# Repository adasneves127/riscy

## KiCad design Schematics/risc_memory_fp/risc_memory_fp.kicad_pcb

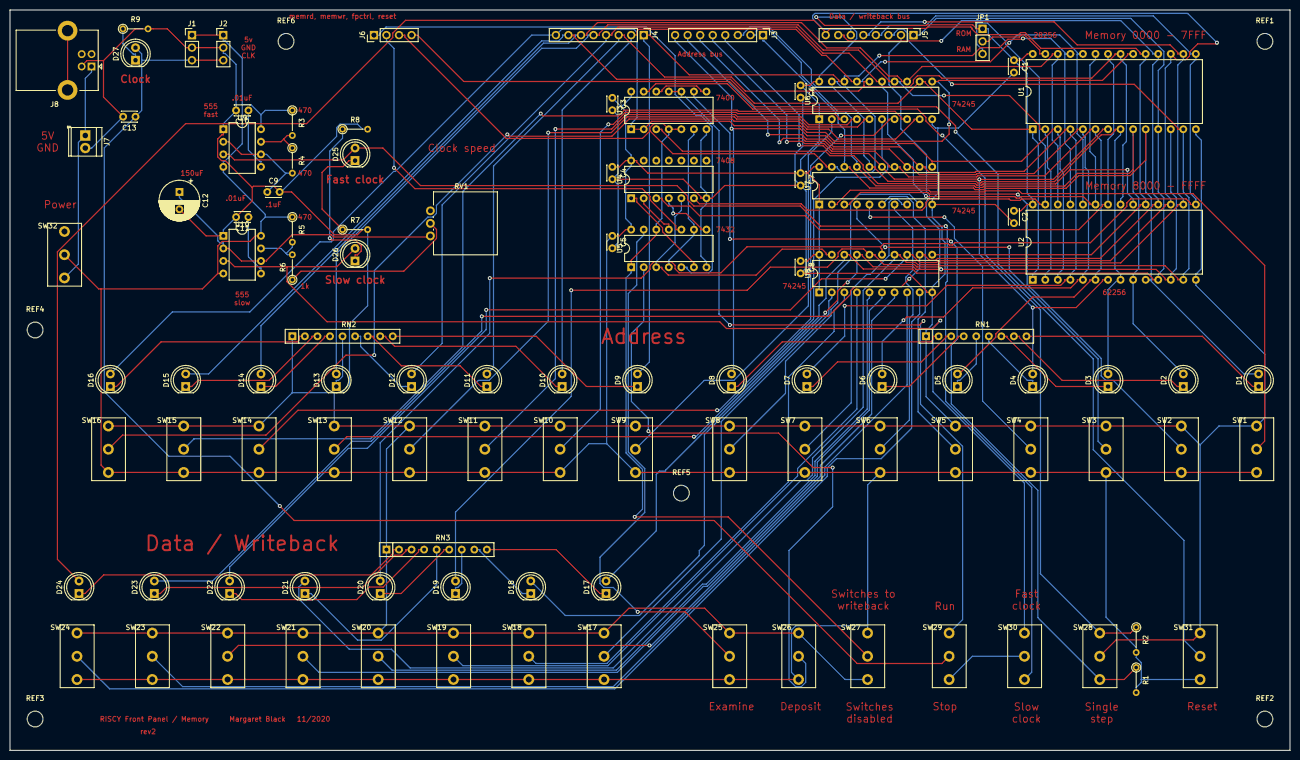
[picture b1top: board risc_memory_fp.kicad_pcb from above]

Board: 2 copper layers, 259.1 x 149.9 mm, 110 parts (0 on the bottom side), 108 nets.

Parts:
C1, C2, C3, C4, C5, C6, C7, C8: C; C_Disc_D3.0mm_W2.0mm_P2.50mm
C9: .1uF; C_Disc_D3.0mm_W2.0mm_P2.50mm
C10, C11: .01uF; C_Disc_D3.0mm_W2.0mm_P2.50mm
C12: 150uF; CP_Radial_D8.0mm_P3.50mm
C13: clocksmoothing; C_Disc_D3.0mm_W2.0mm_P2.50mm
D1, D2, D3, D4, D5, D6, D7, D8, D9, D10, D11, D12, D13, D14, D15, D16, D17, D18, D19, D20, D21, D22, D23, D24: LED; LED_D5.0mm
D25: Fastclock; LED_D5.0mm
D26: Slowclock; LED_D5.0mm
D27: Clock; LED_D5.0mm
J1, J2: Conn_01x03_Female; PinHeader_1x03_P2.54mm_Vertical
J3, J4, J5: Conn_01x08_Female; PinHeader_1x08_P2.54mm_Vertical
J6: Conn_01x04_Female; PinHeader_1x04_P2.54mm_Vertical
J7: Screw_Terminal_01x02; TerminalBlock_TE_282834-2_1x02_P2.54mm_Horizontal
J8: USB_B; USB_B_Lumberg_2411_02_Horizontal
JP1: Jumper_NC_Dual; PinHeader_1x03_P2.54mm_Vertical
R1, R2: 10k; R_Axial_DIN0204_L3.6mm_D1.6mm_P5.08mm_Vertical
R3, R4, R5: 470; R_Axial_DIN0204_L3.6mm_D1.6mm_P5.08mm_Vertical
R6, R7, R8, R9: 1k; R_Axial_DIN0204_L3.6mm_D1.6mm_P5.08mm_Vertical
REF1, REF2, REF3, REF4, REF5, REF6: MountingHole_3.2mm_M3
RN1, RN2, RN3: R_Network08; R_Array_SIP9
RV1: 4.7k; Potentiometer_Vishay_248GJ-249GJ_Single_Vertical
SW1, SW2, SW3, SW4, SW5, SW6, SW7, SW8, SW9, SW10, SW11, SW12, SW13, SW14, SW15, SW16, SW17, SW18, SW19, SW20, SW21, SW22, SW23, SW24, SW25, SW26, SW27, SW28, SW29, SW30, SW31, SW32: SW_SPDT; SPDT_toggle_switch_jameco_pcb_mounting
U1: 28C256; DIP-28_W15.24mm
U2: CY62256-70PC; DIP-28_W15.24mm
U3: 74LS00; DIP-14_W7.62mm
U4: 74LS08; DIP-14_W7.62mm
U5: 74LS32; DIP-14_W7.62mm
U6, U7, U8: 74LS245; DIP-20_W7.62mm
U9, U10: NE555P; DIP-8_W7.62mm

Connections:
+5V: C1.1, C2.1, C3.1, C4.1, C5.1, C6.1, C7.1, C8.1, J1.1, J2.1, JP1.1, R1.2, R2.2, R3.1, R5.1, SW1.3, SW2.3, SW3.3, SW4.3, SW5.3, SW6.3, SW7.3, SW8.3, SW9.3, SW10.3, SW11.3, SW12.3, SW13.3, SW14.3, SW15.3, SW16.3, SW17.3, SW18.3, SW19.3, SW20.3, SW21.3, SW22.3, SW23.3, SW24.3, SW25.3, SW26.3, SW27.1, SW31.3, SW32.2, U1.28, U2.28, U3.14, U4.14, U5.14, U6.1, U6.20, U7.1, U7.20, U8.1, U8.20, U9.4, U9.8, U10.4, U10.8
CLK: C13.1, D27.2, J1.3, J2.3, SW29.2
GND: C1.2, C2.2, C3.2, C4.2, C5.2, C6.2, C7.2, C8.2, C9.2, C10.2, C11.2, C12.2, C13.2, J1.2, J2.2, J7.2, J8.4, R7.2, R8.2, R9.2, RN1.1, RN2.1, RN3.1, SW1.1, SW2.1, SW3.1, SW4.1, SW5.1, SW6.1, SW7.1, SW8.1, SW9.1, SW10.1, SW11.1, SW12.1, SW13.1, SW14.1, SW15.1, SW16.1, SW17.1, SW18.1, SW19.1, SW20.1, SW21.1, SW22.1, SW23.1, SW24.1, SW25.1, SW26.1, SW27.3, SW28.2, SW31.1, U1.14, U2.14, U3.7, U4.7, U5.7, U6.10, U7.10, U8.10, U9.1, U10.1
unnamed: C9.1, R4.2, U9.2, U9.6
unnamed: C10.1, U9.5
unnamed: C11.1, U10.5
unnamed: C12.1, RV1.1, U10.2, U10.6
unnamed: D1.1, RN1.9
unnamed: D2.1, RN1.8
unnamed: D3.1, RN1.7
unnamed: D4.1, RN1.6
unnamed: D5.1, RN1.5
unnamed: D6.1, RN1.4
unnamed: D7.1, RN1.3
unnamed: D8.1, RN1.2
unnamed: D9.1, RN2.9
unnamed: D10.1, RN2.8
unnamed: D11.1, RN2.7
unnamed: D12.1, RN2.6
unnamed: D13.1, RN2.5
unnamed: D14.1, RN2.4
unnamed: D15.1, RN2.3
unnamed: D16.1, RN2.2
unnamed: D17.1, RN3.9
unnamed: D18.1, RN3.8
unnamed: D19.1, RN3.7
unnamed: D20.1, RN3.6
unnamed: D21.1, RN3.5
unnamed: D22.1, RN3.4
unnamed: D23.1, RN3.3
unnamed: D24.1, RN3.2
unnamed: D25.1, R7.1
unnamed: D25.2, SW30.3, U9.3
unnamed: D26.1, R8.1
unnamed: D26.2, SW30.1, U10.3
unnamed: D27.1, R9.1
unnamed: J7.1, J8.1, SW32.3
unnamed: JP1.2, U1.27
unnamed: R1.1, SW28.3, U3.9
unnamed: R2.1, SW28.1, U3.13
unnamed: R3.2, R4.1, U9.7
unnamed: R5.2, R6.2, U10.7
unnamed: R6.1, RV1.2
unnamed: SW1.2, U7.2
unnamed: SW2.2, U7.3
unnamed: SW3.2, U7.4
unnamed: SW4.2, U7.5
unnamed: SW5.2, U7.6
unnamed: SW6.2, U7.7
unnamed: SW7.2, U7.8
unnamed: SW8.2, U7.9
unnamed: SW9.2, U6.2
unnamed: SW10.2, U6.3
unnamed: SW11.2, U6.4
unnamed: SW12.2, U6.5
unnamed: SW13.2, U6.6
unnamed: SW14.2, U6.7
unnamed: SW15.2, U6.8
unnamed: SW16.2, U6.9
unnamed: SW17.2, U8.2
unnamed: SW18.2, U8.3
unnamed: SW19.2, U8.4
unnamed: SW20.2, U8.5
unnamed: SW21.2, U8.6
unnamed: SW22.2, U8.7
unnamed: SW23.2, U8.8
unnamed: SW24.2, U8.9
unnamed: SW29.1, U3.10, U3.11
unnamed: SW29.3, SW30.2
unnamed: U2.20, U3.3
unnamed: U3.6, U5.4, U5.9
unnamed: U3.8, U3.12
unnamed: U4.1, U5.6
unnamed: U4.2, U5.11
unnamed: U4.4, U5.8
addr0: D1.2, J3.1, U1.10, U2.10, U7.18
addr1: D2.2, J3.2, U1.9, U2.9, U7.17
addr2: D3.2, J3.3, U1.8, U2.8, U7.16
addr3: D4.2, J3.4, U1.7, U2.7, U7.15
addr4: D5.2, J3.5, U1.6, U2.6, U7.14
addr5: D6.2, J3.6, U1.5, U2.5, U7.13
addr6: D7.2, J3.7, U1.4, U2.4, U7.12
addr7: D8.2, J3.8, U1.3, U2.3, U7.11
addr8: D9.2, J4.1, U1.25, U2.25, U6.18
addr9: D10.2, J4.2, U1.24, U2.24, U6.17
addr10: D11.2, J4.3, U1.21, U2.21, U6.16
addr11: D12.2, J4.4, U1.23, U2.23, U6.15
addr12: D13.2, J4.5, U1.2, U2.2, U6.14
addr13: D14.2, J4.6, U1.26, U2.26, U6.13
addr14: D15.2, J4.7, U1.1, U2.1, U6.12
addr15: D16.2, J4.8, U1.20, U3.1, U3.2, U6.11
deposit: SW26.2, U5.2
examine: SW25.2, U5.13
fpcontrol: J6.3, SW27.2, U3.4, U3.5, U5.1, U5.12, U6.19, U7.19
memrd: J6.1, U5.5
memwr: J6.2, U5.10
rd: U1.22, U2.22, U4.3
reset: J6.4, SW31.2
switchtowb: U4.5, U5.3, U8.19
wb0: D17.2, J5.1, U1.11, U2.11, U8.18
wb1: D18.2, J5.2, U1.12, U2.12, U8.17
wb2: D19.2, J5.3, U1.13, U2.13, U8.16
wb3: D20.2, J5.4, U1.15, U2.15, U8.15
wb4: D21.2, J5.5, U1.16, U2.16, U8.14
wb5: D22.2, J5.6, U1.17, U2.17, U8.13
wb6: D23.2, J5.7, U1.18, U2.18, U8.12
wb7: D24.2, J5.8, U1.19, U2.19, U8.11
wr: JP1.3, U2.27, U4.6

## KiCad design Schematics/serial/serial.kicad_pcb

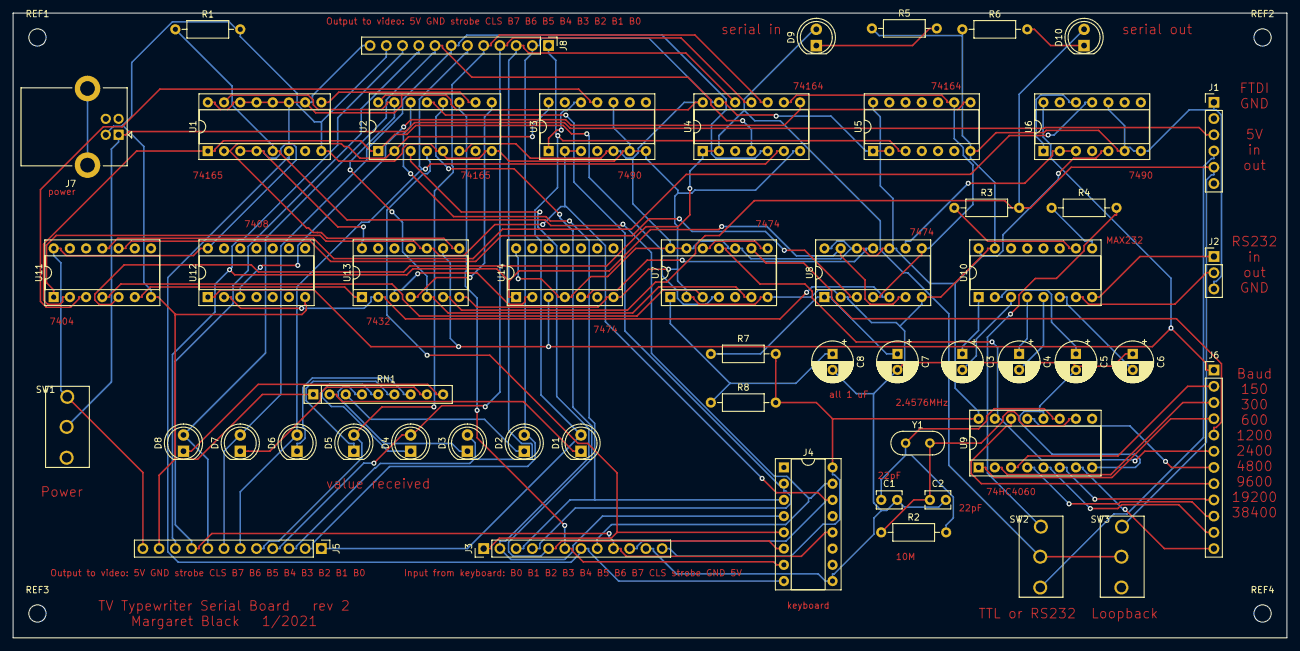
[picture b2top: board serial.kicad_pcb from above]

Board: 2 copper layers, 199.4 x 97.8 mm, 57 parts (0 on the bottom side), 81 nets.

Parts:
C1, C2: 22pF; C_Disc_D3.8mm_W2.6mm_P2.50mm
C3, C4, C5, C6, C7, C8: 1uF; CP_Radial_D6.3mm_P2.50mm
D1, D2, D3, D4, D5, D6, D7, D8, D9, D10: LED; LED_D5.0mm
J1: FTDI; PinHeader_1x06_P2.54mm_Vertical
J2: rs232; PinHeader_1x03_P2.54mm_Vertical
J3: keyboard; PinHeader_1x12_P2.54mm_Vertical
J4: keyboard; DIP-16_W7.62mm_Socket
J5, J8: video; PinHeader_1x12_P2.54mm_Vertical
J6: baudrate; PinHeader_1x12_P2.54mm_Vertical
J7: USB_B; USB_B_Lumberg_2411_02_Horizontal
R1, R3, R4, R5, R6, R7, R8: 1k; R_Axial_DIN0207_L6.3mm_D2.5mm_P10.16mm_Horizontal
R2: 10M; R_Axial_DIN0207_L6.3mm_D2.5mm_P10.16mm_Horizontal
REF1, REF2, REF3, REF4: MountingHole_2.7mm_M2.5
RN1: 1k; R_Array_SIP9
SW1: POWER; SPDT_toggle_switch_jameco_pcb_mounting
SW2: TTLorRS232; SPDT_toggle_switch_jameco_pcb_mounting
SW3: loopback; SPDT_toggle_switch_jameco_pcb_mounting
U1, U2: 74LS165; DIP-16_W7.62mm_Socket
U3, U6: 74LS90; DIP-14_W7.62mm_Socket
U4, U5: 74164; DIP-14_W7.62mm_Socket
U7, U8, U14: 74LS74; DIP-14_W7.62mm_Socket
U9: 74HC4060; DIP-16_W7.62mm_Socket
U10: MAX232; DIP-16_W7.62mm_Socket
U11: 74LS04; DIP-14_W7.62mm_Socket
U12: 74LS08; DIP-14_W7.62mm_Socket
U13: 74LS32; DIP-14_W7.62mm_Socket
Y1: 2.4576MHz; Crystal_HC52-6mm_Vertical

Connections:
+5V: J3.12, J4.16, J5.12, J8.12, R7.2, R8.2, SW1.1, U1.3, U1.4, U1.10, U1.11, U1.12, U1.13, U1.14, U1.16, U2.6, U2.16, U3.5, U4.14, U5.14, U6.5, U7.10, U7.13, U7.14, U8.10, U8.12, U8.14, U9.16, U10.16, U11.14, U12.14, U13.14, U14.4, U14.14
B0_in: J3.1, J4.5, U2.4
B0_out: D1.2, J5.1, J8.1, U5.3
B1_in: J3.2, J4.4, U2.3
B1_out: D2.2, J5.2, J8.2, U4.13, U5.1, U5.2
B2_in: J3.3, J4.3, U2.14
B2_out: D3.2, J5.3, J8.3, U4.12
B3_in: J3.4, J4.2, U2.13
B3_out: D4.2, J5.4, J8.4, U4.11
B4_in: J3.5, J4.6, U2.12
B4_out: D5.2, J5.5, J8.5, U4.10
B5_in: J3.6, J4.7, U2.11
B5_out: D6.2, J5.6, J8.6, U4.6
B6_in: J3.7, J4.8, U1.6
B6_out: D7.2, J5.7, J8.7, U4.5
B7_in: J3.8, J4.15, R1.1, U1.5
B7_out: D8.2, J5.8, J8.8, U4.4
CLS: J3.9, J4.12, J5.9, J8.9
GND: C1.2, C2.2, C5.2, C6.1, C7.2, C8.2, J1.1, J2.3, J3.11, J4.9, J5.11, J7.4, J8.11, R1.2, R5.1, R6.1, RN1.1, U1.8, U2.5, U2.8, U3.6, U3.7, U3.10, U4.7, U5.7, U6.6, U6.7, U6.10, U7.2, U7.7, U8.2, U8.7, U9.8, U9.12, U10.15, U11.7, U12.7, U13.7, U14.7
unnamed: C1.1, R2.2, U9.11, Y1.1
unnamed: C2.1, R2.1, U9.10, Y1.2
unnamed: C3.1, U10.1
unnamed: C3.2, U10.3
unnamed: C4.1, U10.4
unnamed: C4.2, U10.5
unnamed: C5.1, U10.2
unnamed: C6.2, U10.6
unnamed: C7.1, R7.1, U8.1
unnamed: C8.1, R8.1, U7.1
unnamed: D1.1, RN1.2
unnamed: D2.1, RN1.3
unnamed: D3.1, RN1.4
unnamed: D4.1, RN1.5
unnamed: D5.1, RN1.6
unnamed: D6.1, RN1.7
unnamed: D7.1, RN1.8
unnamed: D8.1, RN1.9
unnamed: D9.1, R5.2
unnamed: D10.1, R6.2
unnamed: J1.3, J7.1, SW1.2
unnamed: J1.4, SW2.3
unnamed: J2.1, U10.8
unnamed: J2.2, U10.7
unnamed: J6.2, U9.3
unnamed: J6.3, U9.2
unnamed: J6.4, U9.1
unnamed: J6.5, U7.9
unnamed: J6.6, U7.11, U9.15
unnamed: J6.7, U9.13
unnamed: J6.8, U9.14
unnamed: J6.9, U9.6
unnamed: J6.10, U9.4
unnamed: J6.11, U9.5
unnamed: J6.12, U9.7
unnamed: R3.1, U10.10
unnamed: R4.1, U10.9
unnamed: R4.2, SW2.1
unnamed: U1.1, U2.1, U7.4, U11.2
unnamed: U1.2, U2.2, U3.14, U13.8
unnamed: U1.9, U2.10
unnamed: U1.15, U2.15, U7.6, U13.5
unnamed: U3.1, U3.12
unnamed: U4.9, U5.9, U8.4, U8.8
unnamed: U6.1, U6.12
unnamed: U6.2, U6.3, U8.9
unnamed: U7.8, U7.12
unnamed: U3.11, U11.3
unnamed: U7.3, U11.4
unnamed: U11.6, U13.1
unnamed: U8.3, U11.10
unnamed: U6.11, U11.11
unnamed: U8.5, U12.2, U13.2
unnamed: U4.8, U5.8, U12.3
unnamed: U13.3, U14.2
unnamed: U2.9, U13.4
unnamed: U8.11, U14.5
clock: J6.1, U6.14, U12.1, U13.9, U14.3
serial_in_ttl: D9.2, SW2.2, SW3.2, U4.1, U4.2, U11.5
serial_out_ttl: D10.2, J1.5, R3.2, SW3.1, U13.6
strobe_in: J3.10, J4.14, U3.2, U3.3, U11.1, U13.10
strobe_out: J5.10, J8.10, U8.6, U8.13, U14.1

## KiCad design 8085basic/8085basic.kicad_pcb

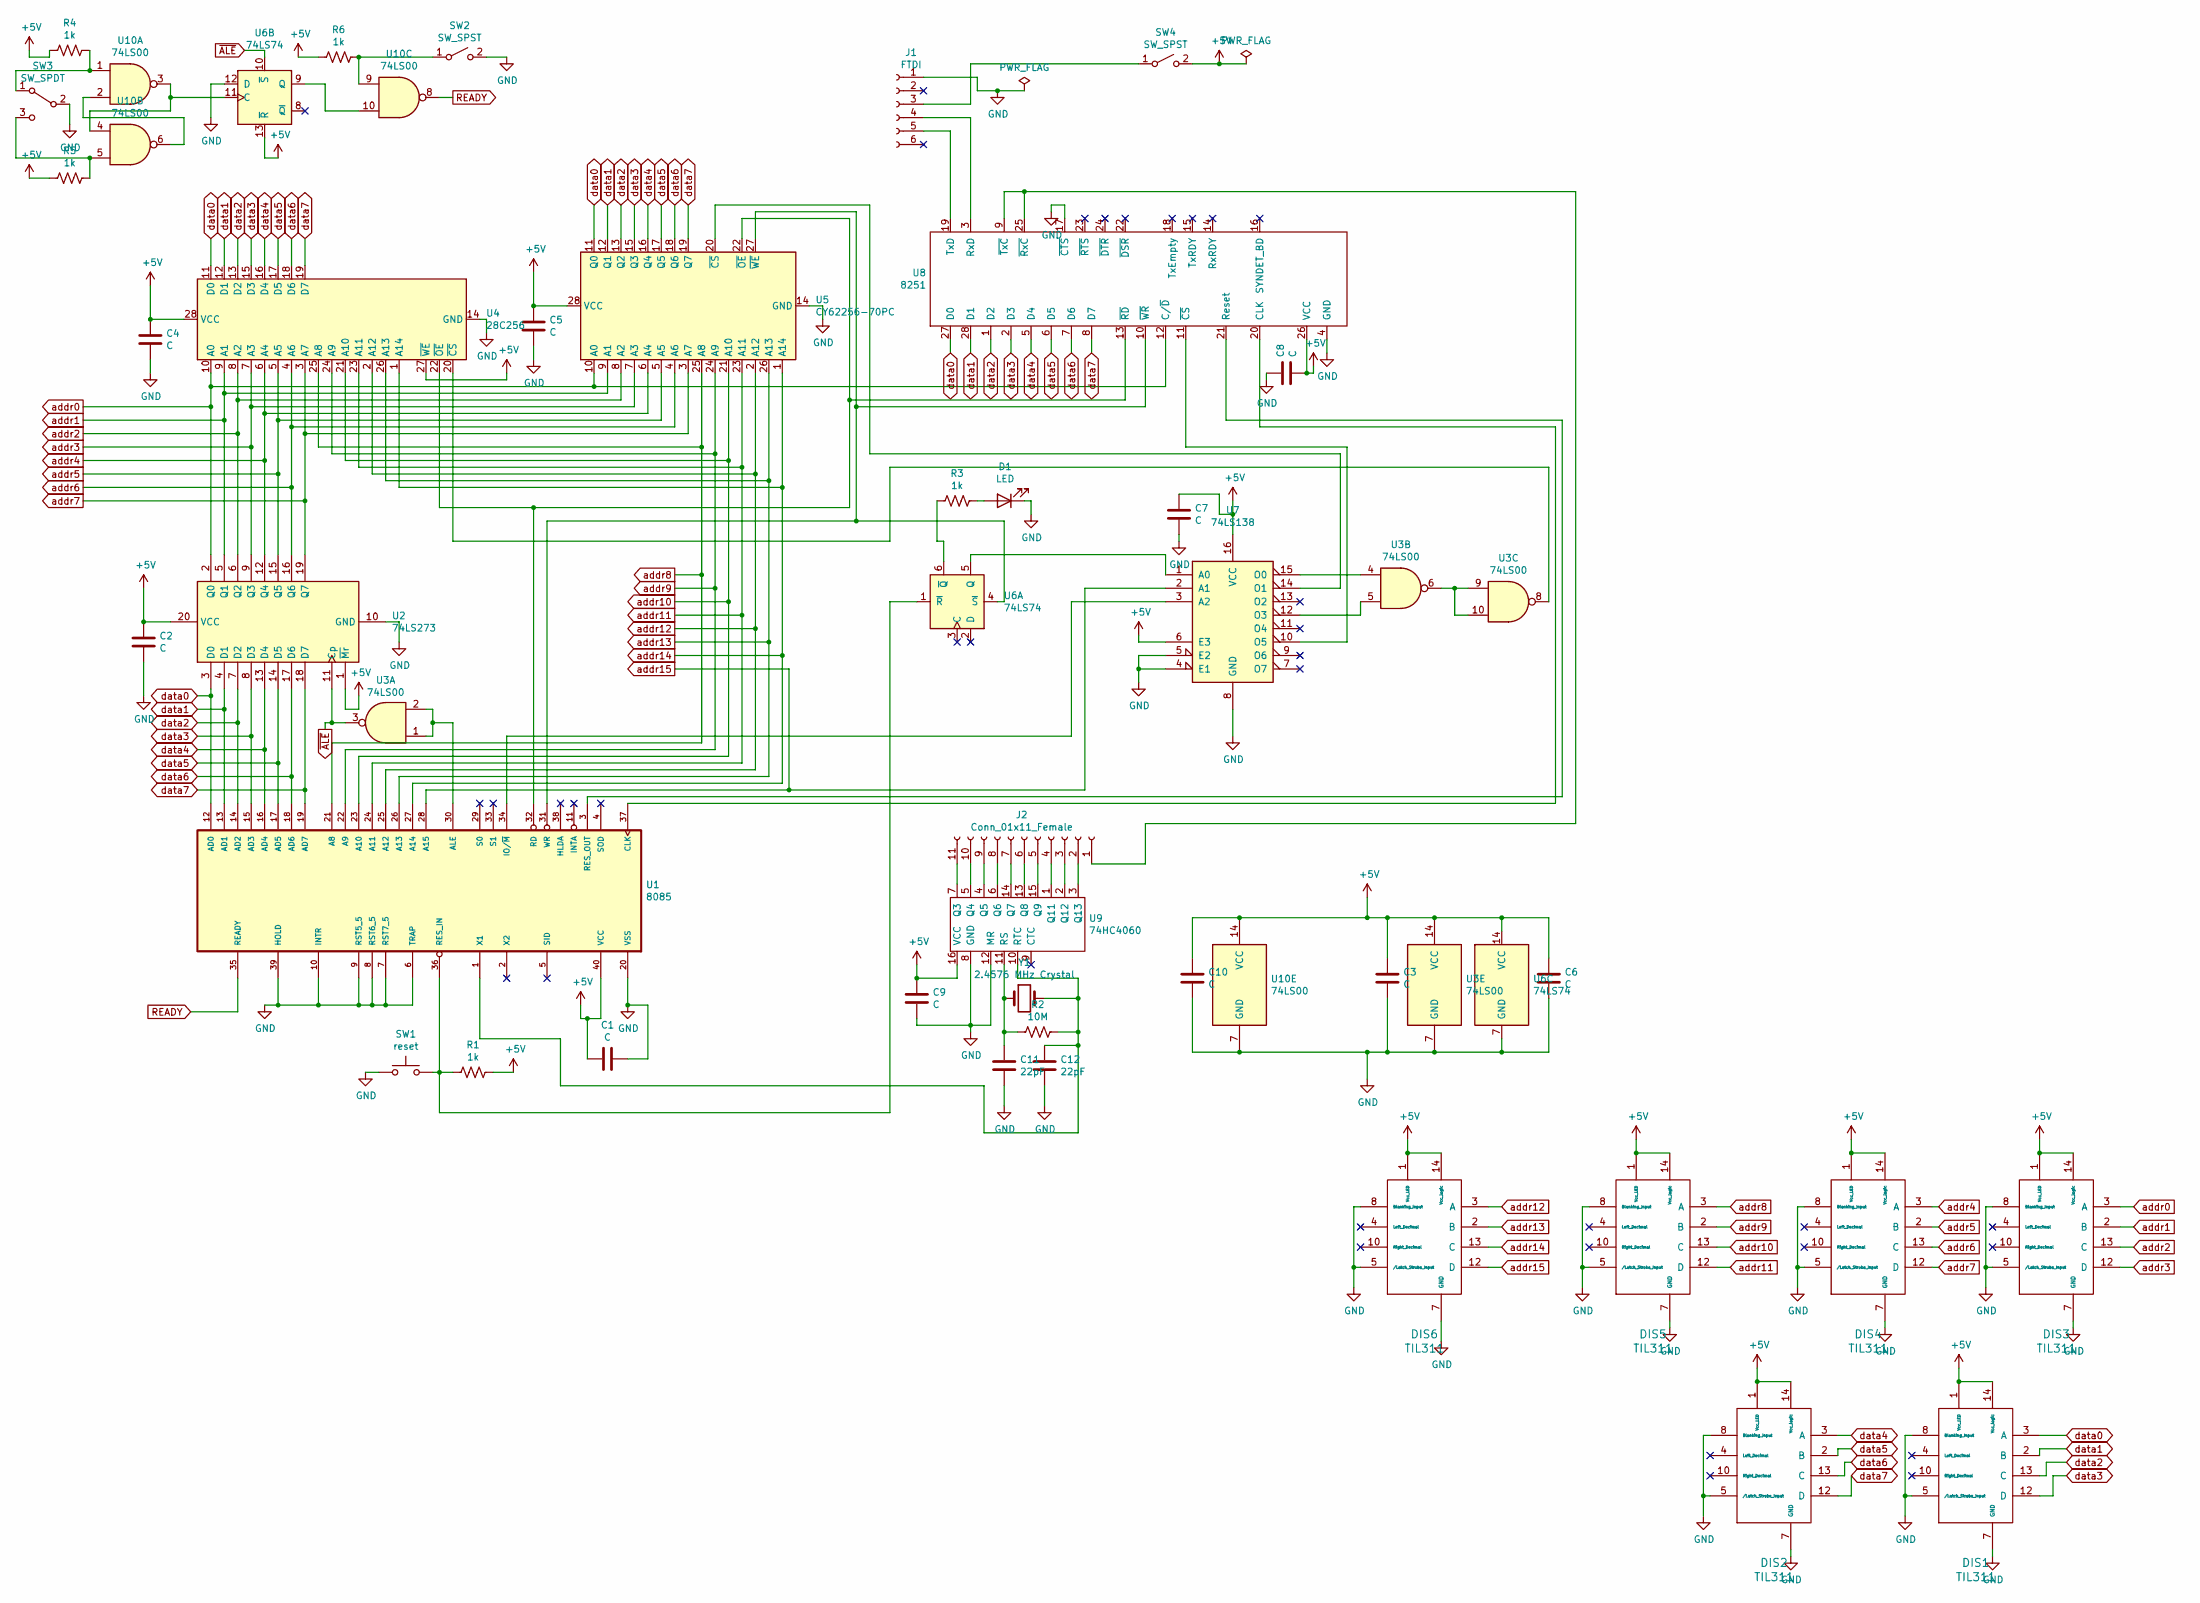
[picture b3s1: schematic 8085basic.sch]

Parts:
C1, C2, C3, C4, C5, C6, C7, C8, C9, C10: C; C_Disc_D3.4mm_W2.1mm_P2.50mm
C11, C12: 22pF; C_Disc_D3.4mm_W2.1mm_P2.50mm
D1: LED; LED_D5.0mm
DIS1, DIS2, DIS3, DIS4, DIS5, DIS6: TIL311; DIP-14_W7.62mm
J1: FTDI; PinHeader_1x06_P2.54mm_Vertical
J2: Conn_01x11_Female; PinSocket_1x11_P2.54mm_Vertical
R1, R3, R4, R5, R6: 1k; R_Axial_DIN0207_L6.3mm_D2.5mm_P10.16mm_Horizontal
R2: 10M; R_Axial_DIN0207_L6.3mm_D2.5mm_P10.16mm_Horizontal
SW1: reset; SW_PUSH_6mm_H4.3mm
SW2, SW4: SW_SPST; SPDT_toggle_switch_jameco_pcb_mounting
SW3: SW_SPDT; SPDT_pushbutton_switch_jameco_pcb_mounting
U1: 8085; DIP-40_W15.24mm
U2: 74LS273; DIP-20_W7.62mm
U3, U10: 74LS00; DIP-14_W7.62mm
U4: 28C256; DIP-28_W15.24mm
U5: CY62256-70PC; DIP-28_W15.24mm
U6: 74LS74; DIP-14_W7.62mm
U7: 74LS138; DIP-16_W7.62mm
U8: 8251; DIP-28_W15.24mm
U9: 74HC4060; DIP-16_W7.62mm
Y1: 2.4576 MHz Crystal; Crystal_HC49-U_Vertical

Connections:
+5V: C1.2, C2.2, C3.2, C4.2, C5.2, C6.2, C7.2, C8.1, C9.2, C10.2, DIS1.1 (Vcc_LED), DIS1.14 (Vcc_logic), DIS2.1 (Vcc_LED), DIS2.14 (Vcc_logic), DIS3.1 (Vcc_LED), DIS3.14 (Vcc_logic), DIS4.1 (Vcc_LED), DIS4.14 (Vcc_logic), DIS5.1 (Vcc_LED), DIS5.14 (Vcc_logic), DIS6.1 (Vcc_LED), DIS6.14 (Vcc_logic), R1.1, R4.2, R5.2, R6.2, SW4.2 (B), U1.40 (VCC), U2.1 (~Mr), U2.20 (VCC), U3.14 (VCC), U4.27 (~WE), U4.28 (VCC), U5.28 (VCC), U6.13 (~R), U6.14 (VCC), U7.6 (E3), U7.16 (VCC), U8.26 (VCC), U9.16 (VCC), U10.14 (VCC)
GND: C1.1, C2.1, C3.1, C4.1, C5.1, C6.1, C7.1, C8.2, C9.1, C10.1, C11.1, C12.1, D1.1 (K), DIS1.5 (/Latch_Strobe_Input), DIS1.7 (GND), DIS1.8 (Blanking_Input), DIS2.5 (/Latch_Strobe_Input), DIS2.7 (GND), DIS2.8 (Blanking_Input), DIS3.5 (/Latch_Strobe_Input), DIS3.7 (GND), DIS3.8 (Blanking_Input), DIS4.5 (/Latch_Strobe_Input), DIS4.7 (GND), DIS4.8 (Blanking_Input), DIS5.5 (/Latch_Strobe_Input), DIS5.7 (GND), DIS5.8 (Blanking_Input), DIS6.5 (/Latch_Strobe_Input), DIS6.7 (GND), DIS6.8 (Blanking_Input), J1.1, SW1.1, SW2.2 (B), SW3.2 (B), U1.6 (TRAP), U1.7 (RST7_5), U1.8 (RST6_5), U1.9 (RST5_5), U1.10 (INTR), U1.20 (VSS), U1.39 (HOLD), U2.10 (GND), U3.7 (GND), U4.14 (GND), U5.14 (GND), U6.7 (GND), U6.12 (D), U7.4 (E1), U7.5 (E2), U7.8 (GND), U8.4 (GND), U8.17 (~CTS), U9.8 (GND), U9.12 (MR), U10.7 (GND)
unnamed: C11.2, R2.2, U9.11 (RS), Y1.1
unnamed: C12.2, R2.1, U1.1 (X1), U9.10 (RTC), Y1.2
unnamed: D1.2 (A), R3.1
unnamed: J1.3, SW4.1 (A)
unnamed: J1.4, U8.3 (RxD)
unnamed: J1.5, U8.19 (TxD)
unnamed: J2.1, U8.9 (~TxC), U8.25 (~RxC)
unnamed: J2.2, U9.3 (Q13)
unnamed: J2.3, U9.2 (Q12)
unnamed: J2.4, U9.1 (Q11)
unnamed: J2.5, U9.15 (Q9)
unnamed: J2.6, U9.13 (Q8)
unnamed: J2.7, U9.14 (Q7)
unnamed: J2.8, U9.6 (Q6)
unnamed: J2.9, U9.4 (Q5)
unnamed: J2.10, U9.5 (Q4)
unnamed: J2.11, U9.7 (Q3)
unnamed: R1.2, SW1.2, U1.36 (RES_IN), U6.1 (~R)
unnamed: R3.2, U6.6 (~Q)
unnamed: R4.1, SW3.1 (A), U10.1
unnamed: R5.1, SW3.3 (C), U10.5
unnamed: R6.1, SW2.1 (A), U10.9
unnamed: U1.3 (RES_OUT), U8.21 (Reset)
unnamed: U1.30 (ALE), U3.1, U3.2
unnamed: U1.31 (WR), U5.27 (~WE), U6.4 (~S), U8.10 (~WR)
unnamed: U1.32 (RD), U4.22 (~OE), U5.22 (~OE), U8.13 (~RD)
unnamed: U1.34 (IO/~M), U7.3 (A2)
unnamed: U1.37 (CLK), U8.20 (CLK)
unnamed: U3.4, U7.15 (O0)
unnamed: U3.5, U7.12 (O3)
unnamed: U3.8, U4.20 (~CS)
unnamed: U3.6, U3.9, U3.10
unnamed: U5.20 (~CS), U7.14 (O1)
unnamed: U6.5 (Q), U7.1 (A0)
unnamed: U7.10 (O5), U8.11 (~CS)
unnamed: U10.2, U10.6
unnamed: U6.11 (C), U10.3, U10.4
unnamed: U6.9 (Q), U10.10
READY: U1.35 (READY), U10.8
addr0: DIS3.3 (A), U2.2 (Q0), U4.10 (A0), U5.10 (A0), U8.12 (C/~D)
addr1: DIS3.2 (B), U2.5 (Q1), U4.9 (A1), U5.9 (A1)
addr2: DIS3.13 (C), U2.6 (Q2), U4.8 (A2), U5.8 (A2)
addr3: DIS3.12 (D), U2.9 (Q3), U4.7 (A3), U5.7 (A3)
addr4: DIS4.3 (A), U2.12 (Q4), U4.6 (A4), U5.6 (A4)
addr5: DIS4.2 (B), U2.15 (Q5), U4.5 (A5), U5.5 (A5)
addr6: DIS4.13 (C), U2.16 (Q6), U4.4 (A6), U5.4 (A6)
addr7: DIS4.12 (D), U2.19 (Q7), U4.3 (A7), U5.3 (A7)
addr8: DIS5.3 (A), U1.21 (A8), U4.25 (A8), U5.25 (A8)
addr9: DIS5.2 (B), U1.22 (A9), U4.24 (A9), U5.24 (A9)
addr10: DIS5.13 (C), U1.23 (A10), U4.21 (A10), U5.21 (A10)
addr11: DIS5.12 (D), U1.24 (A11), U4.23 (A11), U5.23 (A11)
addr12: DIS6.3 (A), U1.25 (A12), U4.2 (A12), U5.2 (A12)
addr13: DIS6.2 (B), U1.26 (A13), U4.26 (A13), U5.26 (A13)
addr14: DIS6.13 (C), U1.27 (A14), U4.1 (A14), U5.1 (A14)
addr15: DIS6.12 (D), U1.28 (A15), U7.2 (A1)
data0: DIS1.3 (A), U1.12 (AD0), U2.3 (D0), U4.11 (D0), U5.11 (Q0), U8.27 (D0)
data1: DIS1.2 (B), U1.13 (AD1), U2.4 (D1), U4.12 (D1), U5.12 (Q1), U8.28 (D1)
data2: DIS1.13 (C), U1.14 (AD2), U2.7 (D2), U4.13 (D2), U5.13 (Q2), U8.1 (D2)
data3: DIS1.12 (D), U1.15 (AD3), U2.8 (D3), U4.15 (D3), U5.15 (Q3), U8.2 (D3)
data4: DIS2.3 (A), U1.16 (AD4), U2.13 (D4), U4.16 (D4), U5.16 (Q4), U8.5 (D4)
data5: DIS2.2 (B), U1.17 (AD5), U2.14 (D5), U4.17 (D5), U5.17 (Q5), U8.6 (D5)
data6: DIS2.13 (C), U1.18 (AD6), U2.17 (D6), U4.18 (D6), U5.18 (Q6), U8.7 (D6)
data7: DIS2.12 (D), U1.19 (AD7), U2.18 (D7), U4.19 (D7), U5.19 (Q7), U8.8 (D7)
~ALE: U2.11 (Cp), U3.3, U6.10 (~S)

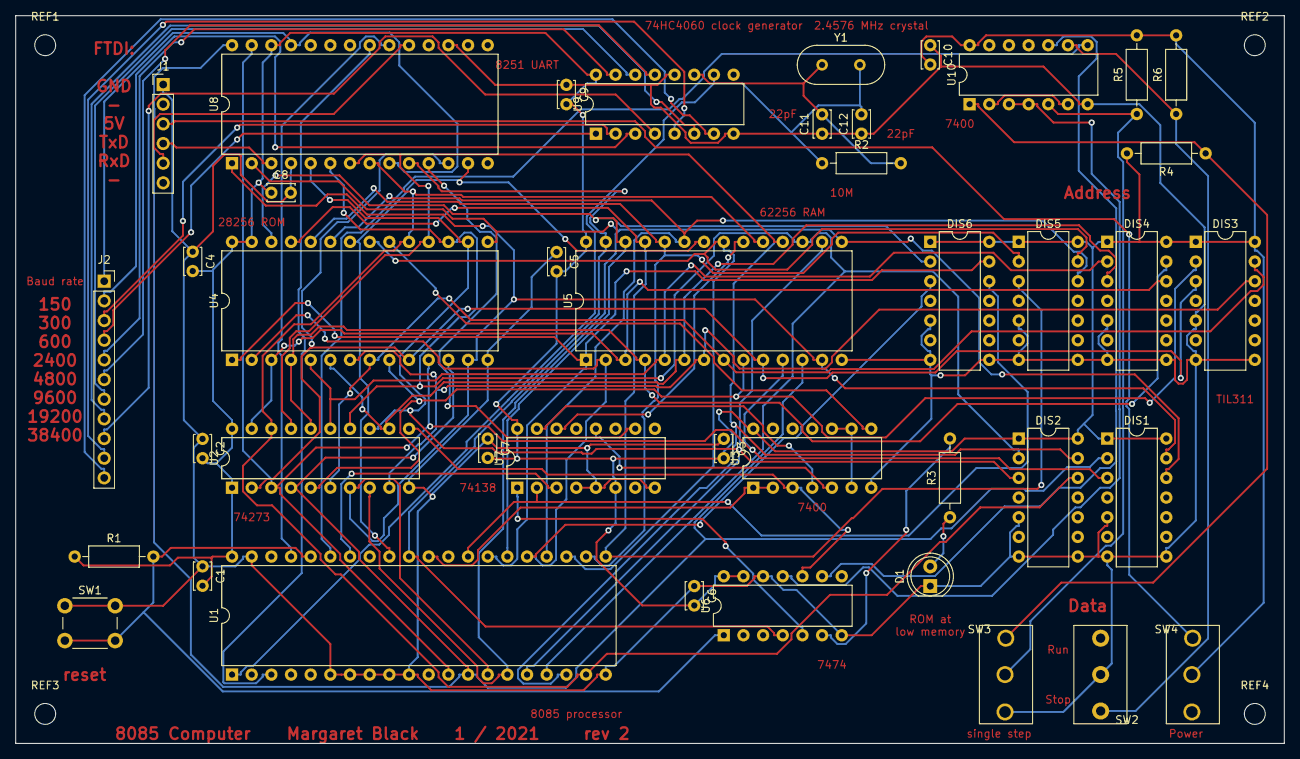
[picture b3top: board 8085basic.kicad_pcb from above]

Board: 2 copper layers, 163.8 x 94.0 mm, 46 parts (0 on the bottom side), 66 nets.

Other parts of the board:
REF1, REF2, REF3, REF4: MountingHole_2.7mm_M2.5
